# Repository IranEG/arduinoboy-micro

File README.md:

# Arduinoboy-micro

A MIDI adapter for the Gameboy.

Uses a Sparkfun Pro Micro and TLP2361 optoisolator.

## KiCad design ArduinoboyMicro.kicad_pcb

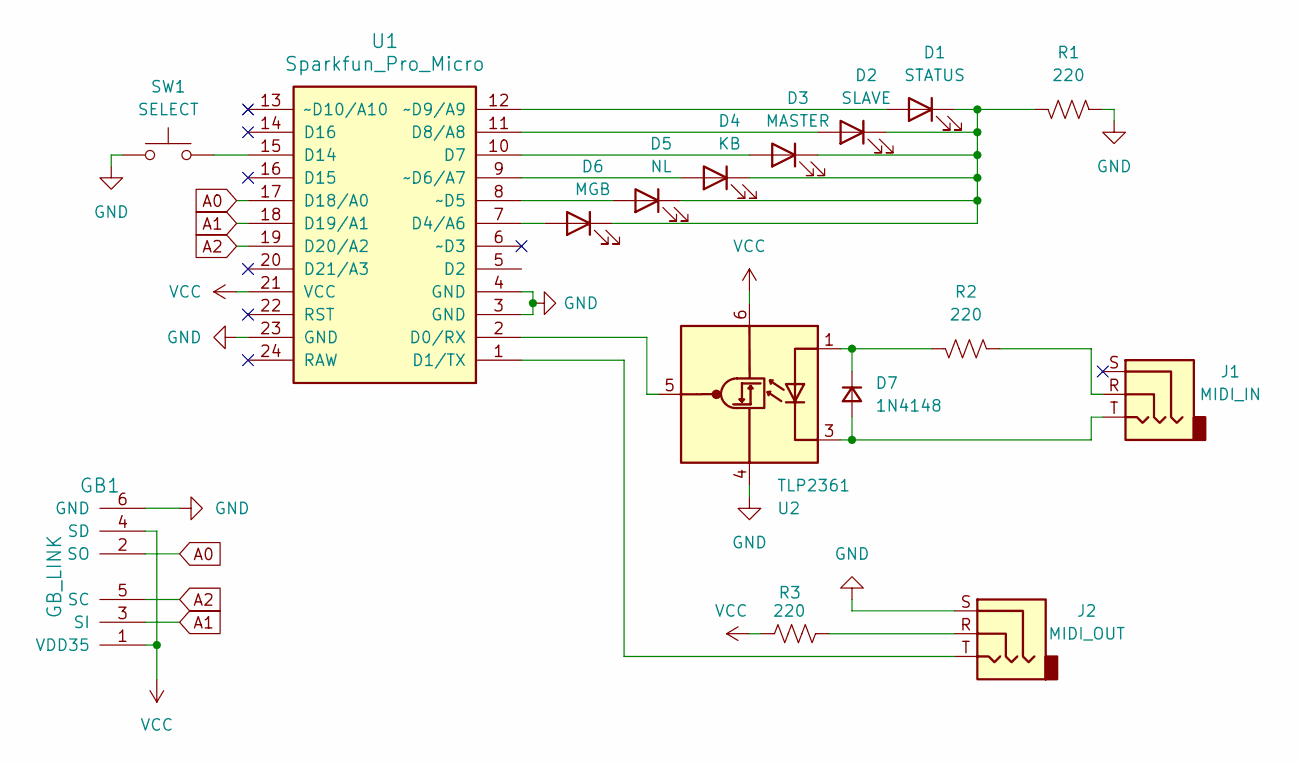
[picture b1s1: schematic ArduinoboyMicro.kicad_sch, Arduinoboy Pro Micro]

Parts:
D1: STATUS; LED_0805_2012Metric_Pad1.15x1.40mm_HandSolder
D2: SLAVE; LED_0805_2012Metric_Pad1.15x1.40mm_HandSolder
D3: MASTER; LED_0805_2012Metric_Pad1.15x1.40mm_HandSolder
D4: KB; LED_0805_2012Metric_Pad1.15x1.40mm_HandSolder
D5: NL; LED_0805_2012Metric_Pad1.15x1.40mm_HandSolder
D6: MGB; LED_0805_2012Metric_Pad1.15x1.40mm_HandSolder
D7: 1N4148; D_0805_2012Metric_Pad1.15x1.40mm_HandSolder
GB1: GB_LINK; gbc-link-socket
J1: MIDI_IN; STX3000
J2: MIDI_OUT; STX3000
R1, R2, R3: 220; R_0805_2012Metric_Pad1.20x1.40mm_HandSolder
SW1: SELECT; SW_Tactile_SPST_NO_Straight_CK_PTS636Sx25SMTRLFS
U1: Sparkfun_Pro_Micro
U2: TLP2361; SO-5_4.4x3.6mm_P1.27mm

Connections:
A0: GB1.2 (SO), U1.17 (D18/A0)
A1: GB1.3 (SI), U1.18 (D19/A1)
A2: GB1.5 (SC), U1.19 (D20/A2)
GND: GB1.6 (GND), J2.S, R1.2, SW1.1, U1.3 (GND), U1.4 (GND), U1.23 (GND), U2.4 (GND)
unnamed: D1.2 (A), U1.12 (~D9/A9)
unnamed: D1.1 (K), D2.1 (K), D3.1 (K), D4.1 (K), D5.1 (K), D6.1 (K), R1.1
unnamed: D2.2 (A), U1.11 (D8/A8)
unnamed: D3.2 (A), U1.10 (D7)
unnamed: D4.2 (A), U1.9 (~D6/A7)
unnamed: D5.2 (A), U1.8 (~D5)
unnamed: D6.2 (A), U1.7 (D4/A6)
unnamed: D7.2 (A), J1.T, U2.3 (K)
unnamed: D7.1 (K), R2.2, U2.1 (A)
unnamed: J1.R, R2.1
unnamed: J2.R, R3.2
unnamed: U1.2 (D0/RX), U2.5 (VO)
unnamed: J2.T, U1.1 (D1/TX)
unnamed: SW1.2, U1.15 (D14)
VCC: GB1.1 (VDD35), GB1.4 (SD), R3.1, U1.21 (VCC), U2.6 (VDD)

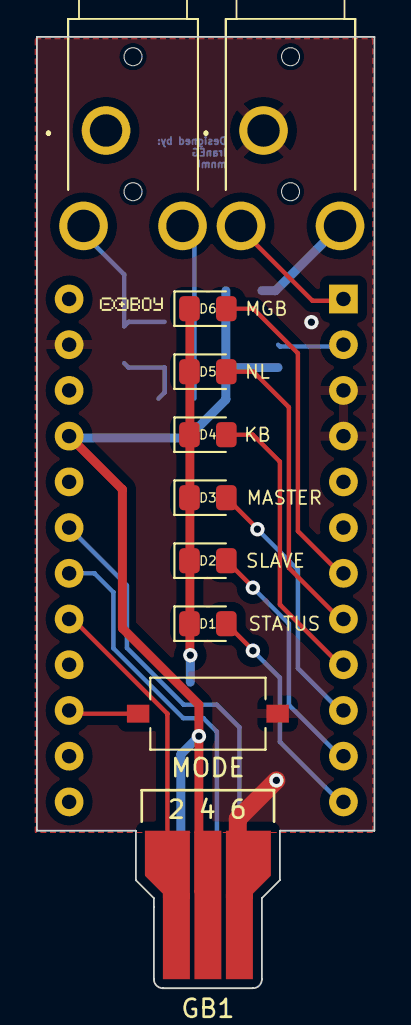
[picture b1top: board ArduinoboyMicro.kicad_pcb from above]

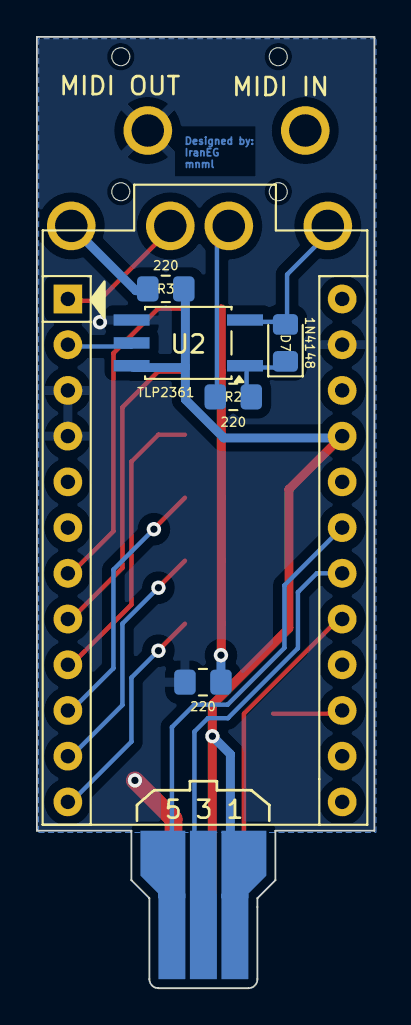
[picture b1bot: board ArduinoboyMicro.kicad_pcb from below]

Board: 2 copper layers, 18.8 x 52.9 mm, 16 parts (6 on the bottom side), 19 nets.

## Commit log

2024-12-28 Adds README and images
2024-12-28 Updates README
